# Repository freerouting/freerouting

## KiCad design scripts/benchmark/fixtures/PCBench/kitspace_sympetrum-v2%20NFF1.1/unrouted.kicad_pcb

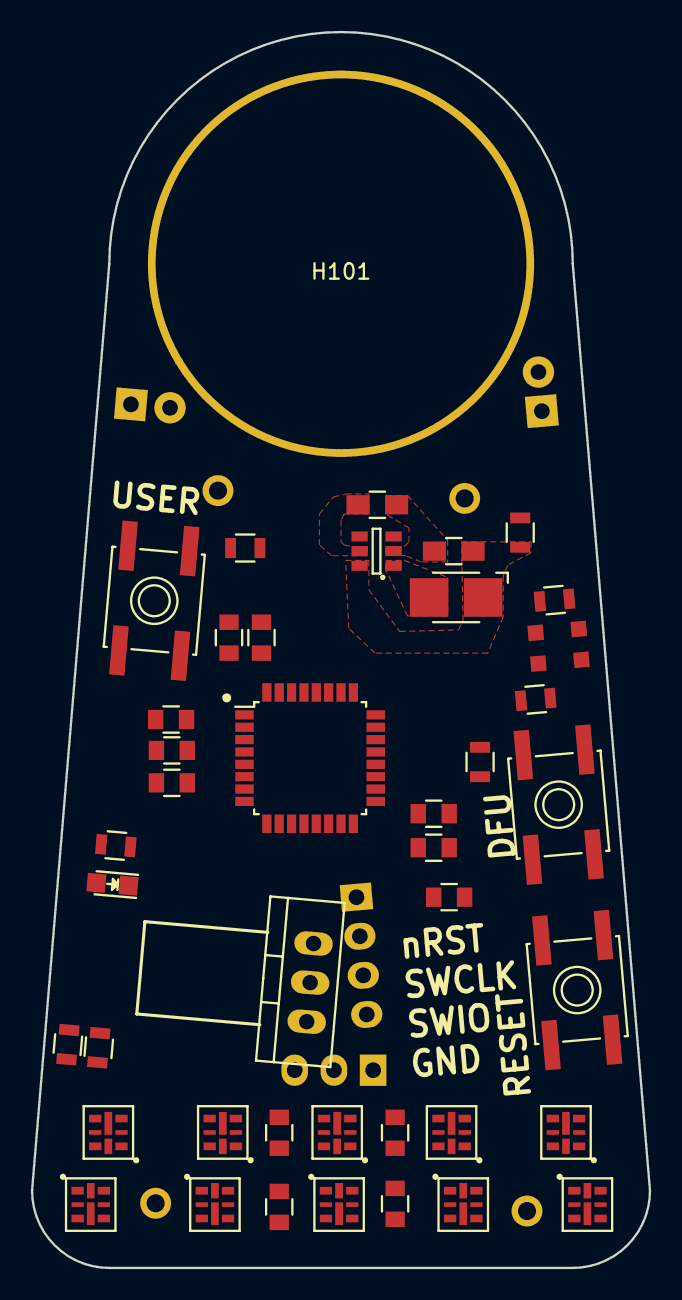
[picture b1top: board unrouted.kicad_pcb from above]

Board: 2 copper layers, 40.0 x 80.0 mm, 49 parts (0 on the bottom side), 43 nets, no tracks yet.

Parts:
B301, B302: BCAAAPC
C101, C102: 0.1µF; C_0805
C103: 10nF; C_0805
C104, C106: 10µF; C_0805
C105: 1µF; C_0805
C107, C108: 100nF; C_0805
C201, C202, C203, C204: 22µF; C_0805
C301, C302: 4.7uF; C_0805_HandSoldering
D101: USER_LED; LED_0805
D102, D103: IR12-21C/TR8; Everlight-IR12-21C-TR8
H101: Hole_-_24mm; Hole-24mm
JP301: JP_POWER; Socket_Strip_Straight_1x02
L301: 4.7uH; Inductor_1212
P101: PROG_HEADER; Pin_Header_Straight_1x04
P102: USART2; Pin_Header_Straight_1x03
P301: DBG_PWR; Pin_Header_Straight_1x02
R1, R102: 10kΩ; R_0805
R101: 1kΩ; R_0805
R103, R104, R105: 0Ω; R_0805
R106: 36Ω; R_0805
R301: 1MΩ; R_0805
SW1: RESET; SW_SPST_EVQP0_DPLIT
SW2: DFU; SW_SPST_EVQP0_DPLIT
SW103: USER; SW_SPST_EVQP0_DPLIT
U101: STM32F051K8T6; LQFP-32_7x7mm_Pitch0.8mm
U102: TSSP58P38; TO-220_Neutral123_Vertical_LayDown
U201, U202, U203, U204, U205, U206, U207, U208, U209, U210: APA102_2020; APA102_2020_LED_Complex_Split
U301: AAT1217-3.3; SOT-23-6

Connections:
+3V3: C103.1, C104.1, C105.1, C106.1, C107.1, C108.1, C201.1, C202.1, C203.1, C204.1, C302.1, P301.1, R102.2, SW2.3, U101.1, U101.5, U101.17, U102.3, U201.7, U202.7, U203.7, U204.7, U205.7, U206.7, U207.7, U208.7, U209.7, U210.7, U301.5
+BATT: B302.1, JP301.1
/IR_RX: U101.7, U102.1
/IR_TX: D102.2, U101.13
/LEDArray/MOSI-IN: R104.1, U201.4
/LEDArray/SCK-IN: R105.1, U201.5
/LED_CLK: R105.2, U101.26
/LED_MOSI: R104.2, U101.28
/Power/VIN: C301.1, JP301.2, L301.1, R301.1, U301.6
/SWDCLK: P101.2, U101.24
/SWDIO: P101.3, U101.23
/USART2_RX: P102.1, U101.9
/USART2_TX: P102.2, U101.8
/USER_BUTTON: C102.1, R102.1, SW103.1, SW103.3, U101.6
/USER_LED: R103.2, U101.11
/nRST: C101.1, P101.1, SW1.2, U101.4
GND: B301.2, C101.2, C102.2, C103.2, C104.2, C105.2, C106.2, C107.2, C108.2, C201.2, C202.2, C203.2, C204.2, C301.2, C302.2, D101.1, P101.4, P102.3, P301.2, R101.2, R106.1, SW1.3, SW103.4, U101.16, U101.32, U102.2, U201.8, U202.8, U203.8, U204.8, U205.8, U206.8, U207.8, U208.8, U209.8, U210.8, U301.2
unnamed: B301.1, B302.2
unnamed: D101.2, R103.1
unnamed: D102.1, D103.2
unnamed: D103.1, R106.2
unnamed: L301.2, U301.1
unnamed: R1.1, SW2.2, SW2.4
unnamed: R1.2, R101.1, U101.31
unnamed: R301.2, U301.4
unnamed: U201.2, U203.5
unnamed: U201.3, U203.4
unnamed: U202.2, U204.5
unnamed: U202.3, U204.4
unnamed: U202.4, U209.3
unnamed: U202.5, U209.2
unnamed: U203.2, U205.5
unnamed: U203.3, U205.4
unnamed: U204.2, U206.5
unnamed: U204.3, U206.4
unnamed: U205.2, U207.5
unnamed: U205.3, U207.4
unnamed: U206.2, U208.5
unnamed: U206.3, U208.4
unnamed: U207.2, U209.5
unnamed: U207.3, U209.4
unnamed: U208.2, U210.5
unnamed: U208.3, U210.4

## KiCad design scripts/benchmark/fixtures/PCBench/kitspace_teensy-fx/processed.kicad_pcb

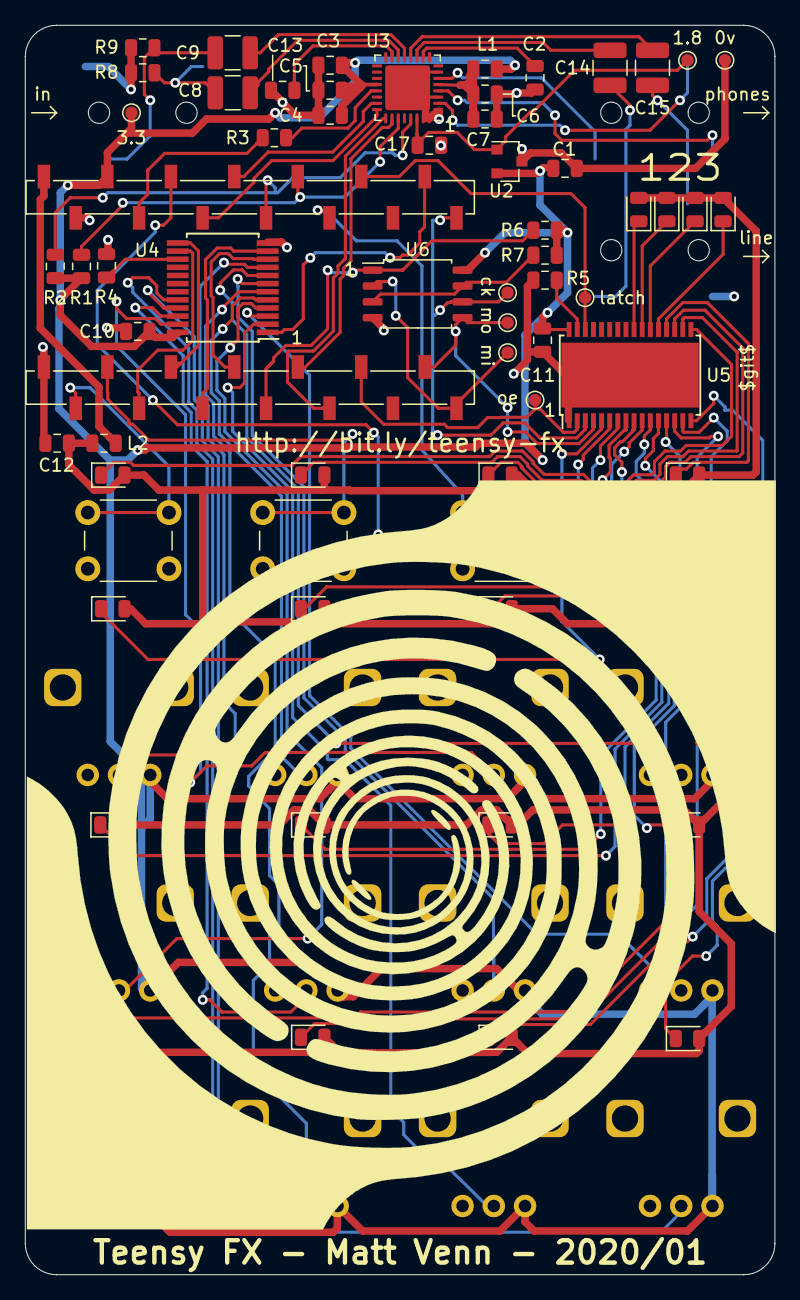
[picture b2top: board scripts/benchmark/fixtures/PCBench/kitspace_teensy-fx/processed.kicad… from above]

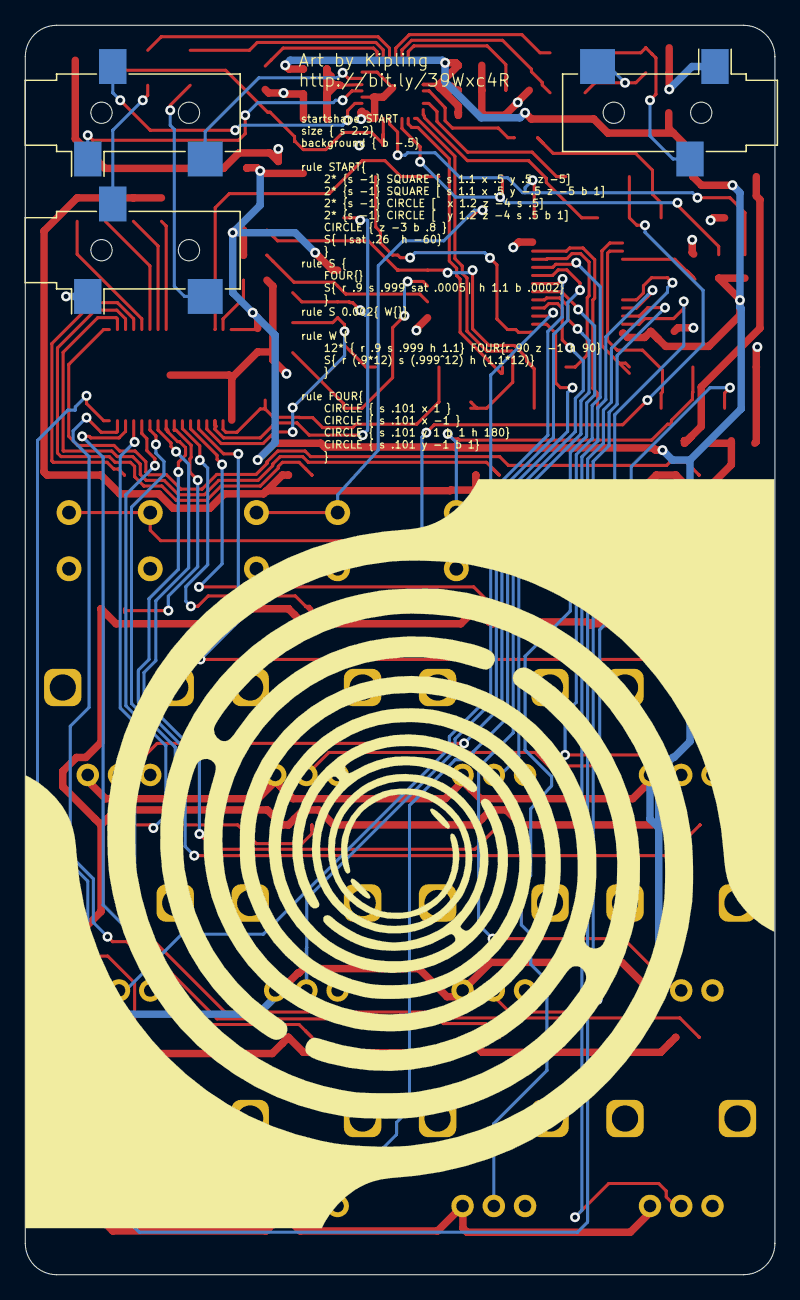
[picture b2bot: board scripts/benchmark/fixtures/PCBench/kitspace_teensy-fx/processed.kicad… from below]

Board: 4 copper layers, 60.0 x 100.0 mm, 80 parts (3 on the bottom side), 77 nets.

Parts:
C1, C3, C6, C10, C11, C12, C17: 2.2uF; C_0805_2012Metric
C2, C4, C5, C7, C13: 0.1uF; C_0805_2012Metric
C8, C9, C14, C15: 1uF; C_1210_3225Metric
D1, D2, D3, D4, D5, D6, D7, D8, D9, D10, D11, D12, D13, D14, D15, D16, D17, D18, D19, D20: LED; LED_0805_2012Metric
J1, J2, J3: AudioJack3_Ground; Jack_3.5mm_CUI_SJ-3523-SMT_Horizontal
L1, L2: 600R; L_0805_2012Metric
R1, R2: 2.2K; R_0805_2012Metric
R3: 100R; R_0805_2012Metric
R4, R6, R7: 10k; R_0805_2012Metric
R5: 4.7k; R_0805_2012Metric
R8, R9: 100k; R_0805_2012Metric
RV1, RV2, RV3, RV4, RV5, RV6, RV7, RV8, RV9, RV10, RV11, RV12: R_POT; Potentiometer_Alps_RK09L_Single_Vertical
SW1, SW2, SW3, SW4: Switch_SW_Push; SW_PUSH_6mm
TP1, TP2, TP3, TP4, TP5, TP6, TP7, TP8: TestPoint; TestPoint_Pad_D1.0mm
U1: Teensy4.0; teensy4smt
U2: MCP1811A; SOT-23
U3: SGTL5000; QFN-32-1EP_5x5mm_P0.5mm_EP3.6x3.6mm
U4: 4067; SSOP-24_5.3x8.2mm_P0.65mm
U5: TLC5947DAP; HTSSOP-32-1EP_6.1x11mm_P0.65mm_EP5.2x11mm_Mask4.11x4.36mm
U6: W25Q128JVS; SOIC-8_5.23x5.23mm_P1.27mm

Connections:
+1V8: C17.1, TP7.1, U2.1, U3.30
+3V3: C1.1, C3.1, C4.1, C5.1, C10.1, C11.1, L1.1, R1.1, R2.1, R6.1, R7.1, RV1.1, RV2.1, RV3.1, RV4.1, RV5.1, RV6.1, RV7.1, RV8.1, RV9.1, RV10.1, RV11.1, RV12.1, TP6.1, U1.31, U2.2, U3.20, U4.24, U5.32, U6.8
+5V: L2.1, U1.33
+5VA: C12.1, D1.2, D2.2, D3.2, D4.2, D5.2, D6.2, D7.2, D8.2, D9.2, D10.2, D11.2, D12.2, D13.2, D14.2, D15.2, D16.2, D17.2, D18.2, D19.2, D20.2, L2.2
/SGTL audio/filter_audio_3v3: C6.1, C7.1, L1.2, U3.5
/mem_cs: R6.2, U1.8, U6.1
/pots buttons & LEDs/a0: RV1.2, U4.9
/pots buttons & LEDs/a1: RV4.2, U4.8
/pots buttons & LEDs/a2: RV7.2, U4.7
/pots buttons & LEDs/a3: RV10.2, U4.6
/pots buttons & LEDs/a4: RV2.2, U4.5
/pots buttons & LEDs/a5: RV5.2, U4.4
/pots buttons & LEDs/a6: RV8.2, U4.3
/pots buttons & LEDs/a7: RV11.2, U4.2
/pots buttons & LEDs/a8: RV3.2, U4.23
/pots buttons & LEDs/a9: RV6.2, U4.22
/pots buttons & LEDs/a10: RV9.2, U4.21
/pots buttons & LEDs/a11: RV12.2, U4.20
BCLK: U1.28, U3.24
GND: C1.2, C2.2, C3.2, C4.2, C5.2, C6.2, C7.2, C10.2, C11.2, C12.2, C13.2, C17.2, J1.S, J3.S, R4.2, R5.2, R8.2, R9.1, RV1.3, RV2.3, RV3.3, RV4.3, RV5.3, RV6.3, RV7.3, RV8.3, RV9.3, RV10.3, RV11.3, RV12.3, SW1.2, SW2.2, SW3.2, SW4.2, TP8.1, U1.1, U1.32, U2.3, U3.1, U3.3, U3.7, U3.31, U3.32, U3.33, U4.12, U5.1, U5.33, U6.4
I2S_IN: U1.10, U3.25
I2S_OUT: U1.9, U3.26
LRCLK: U1.27, U3.23
MCLK: R3.2, U1.30
MISO: TP5.1, U1.14, U6.2
MOSI: TP3.1, U1.13, U5.4, U6.5
unnamed: C2.1, U3.10
unnamed: C8.1, U3.14
unnamed: C8.2, J1.T, R8.1
unnamed: C9.1, U3.13
unnamed: C9.2, J1.R, R9.2
unnamed: C13.1, U3.15
unnamed: C14.1, U3.11
unnamed: C14.2, J3.T
unnamed: C15.1, U3.12
unnamed: C15.2, J3.R
unnamed: D1.1, U5.5
unnamed: D2.1, U5.6
unnamed: D3.1, U5.7
unnamed: D4.1, U5.8
unnamed: D5.1, U5.9
unnamed: D6.1, U5.10
unnamed: D7.1, U5.11
unnamed: D8.1, U5.12
unnamed: D9.1, U5.13
unnamed: D10.1, U5.14
unnamed: D11.1, U5.15
unnamed: D12.1, U5.16
unnamed: D13.1, U5.17
unnamed: D14.1, U5.18
unnamed: D15.1, U5.19
unnamed: D16.1, U5.20
unnamed: D17.1, U5.21
unnamed: D18.1, U5.22
unnamed: D19.1, U5.23
unnamed: D20.1, U5.24
unnamed: J2.R, U3.2
unnamed: J2.S, U3.4
unnamed: J2.T, U3.6
unnamed: R3.1, U3.21
unnamed: R4.1, U4.15
unnamed: R5.1, U5.31
unnamed: R7.2, U6.3, U6.7
SCL: R2.2, U1.26, U3.29
SCLK: TP1.1, U1.20, U5.3, U6.6
SDA: R1.2, U1.25, U3.27
led_latch: TP4.1, U1.23, U5.30
led_oe: TP2.1, U1.11, U5.2
pot_b0: U1.7, U4.10
pot_b1: U1.6, U4.11
pot_b2: U1.4, U4.14
pot_b3: U1.5, U4.13
pot_multiplex: U1.21, U4.1
sw_1: SW1.1, U1.2
sw_2: SW2.1, U1.3
sw_3: SW3.1, U1.24
sw_4: SW4.1, U1.29

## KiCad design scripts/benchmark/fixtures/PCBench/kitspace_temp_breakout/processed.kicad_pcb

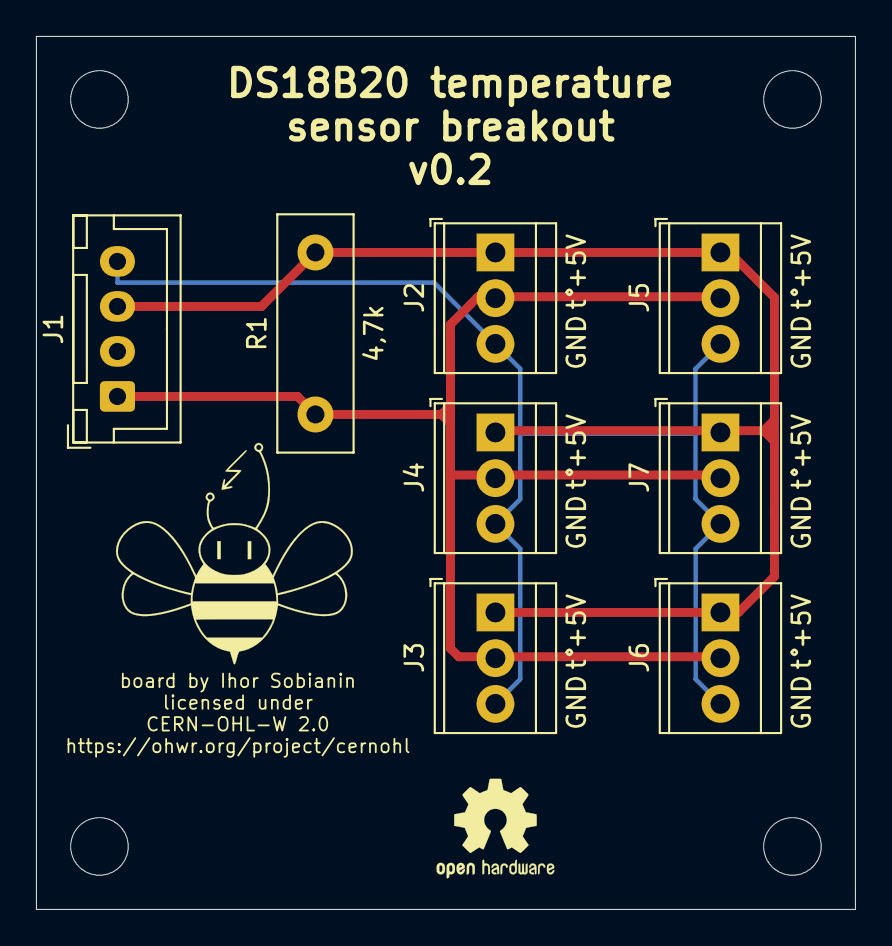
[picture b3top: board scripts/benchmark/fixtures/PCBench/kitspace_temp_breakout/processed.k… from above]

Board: 2 copper layers, 45.5 x 48.5 mm, 8 parts (0 on the bottom side), 3 nets.

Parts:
J1: Conn_01x04; JST_XH_B4B-XH-A_1x04_P2.50mm_Vertical
J2, J3, J4, J5, J6, J7: Conn_01x03; TerminalBlock_TE_282834-3_1x03_P2.54mm_Horizontal
R1: 4,7k; R_Box_L13.0mm_W4.0mm_P9.00mm

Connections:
+5V: J1.3, J2.1, J3.1, J4.1, J5.1, J6.1, J7.1, R1.2
GND: J1.4, J2.3, J3.3, J4.3, J5.3, J6.3, J7.3
esp_pin: J1.1, J2.2, J3.2, J4.2, J5.2, J6.2, J7.2, R1.1

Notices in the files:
scripts/benchmark/fixtures/PCBench/kitspace_temp_breakout/processed.kicad_pcb:
licensed under
CERN-OHL-W 2.0
